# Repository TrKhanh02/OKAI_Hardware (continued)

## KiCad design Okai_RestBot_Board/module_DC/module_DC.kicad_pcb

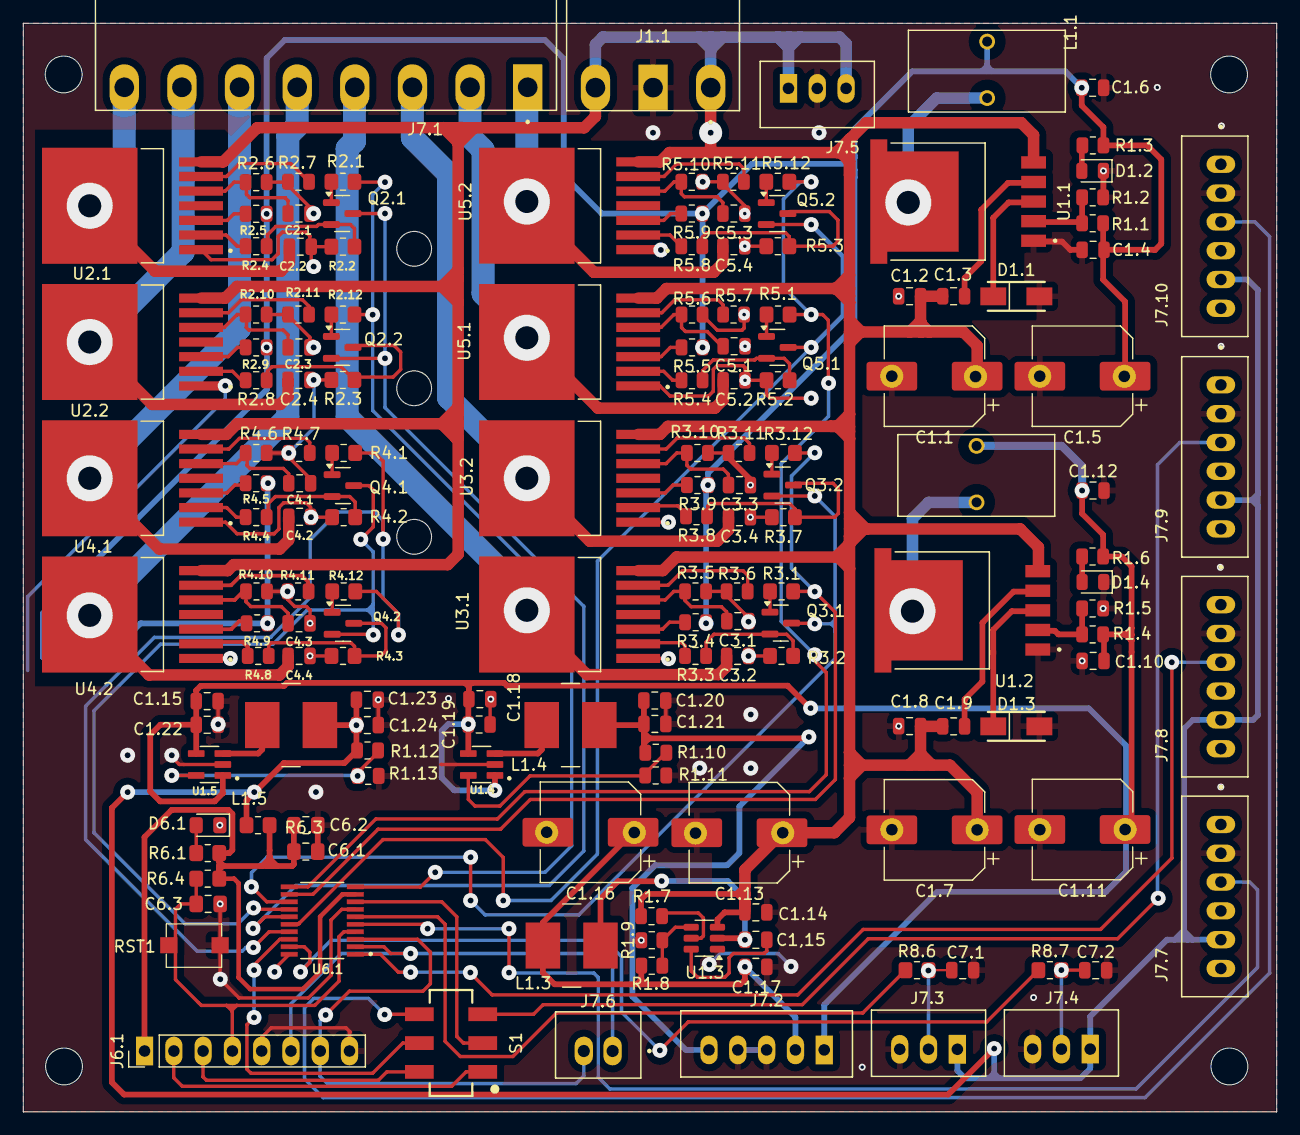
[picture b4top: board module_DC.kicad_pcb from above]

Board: 2 copper layers, 108.8 x 94.4 mm, 158 parts (0 on the bottom side), 102 nets.

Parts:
C1,15, C1.2, C1.6, C1.8, C1.12, C1.14, C1.19, C1.21, C1.22, C1.24, C2.1, C2.3, C3.1, C3.3, C4.1, C4.3, C5.1, C5.3, C7.1, C7.2: 104; C_0805_2012Metric
C1.1, C1.5, C1.7, C1.11, C1.13, C1.16: 220uF/25V; CP_Elec_8x10.5
C1.3, C1.4, C1.9, C1.10, C1.15, C1.17, C1.18, C1.20, C1.23, C2.2, C2.4, C3.2, C3.4, C4.2, C4.4, C5.2, C5.4: 106; C_0805_2012Metric
C6.1, C6.3: 104; C_0805_2012Metric_Pad1.18x1.45mm_HandSolder
C6.2: 10uF; C_0805_2012Metric_Pad1.18x1.45mm_HandSolder
D1.1, D1.3: SS54-HF; DIOM5025X220N
D1.2, D1.4: LED; LED_0805_2012Metric
D6.1: LED_Small_Filled; LED_0805_2012Metric_Pad1.15x1.40mm_HandSolder
J1.1: Nguon IN; CUI_TBP04R1-500-03BE
J6.1: Bootloader; PinHeader_1x08_P2.54mm_Vertical
J7.1: DC_12V; CUI_TBP04R1-500-08BE
J7.2: Nguon DK; JST_B5B-XH-A
J7.3: ROTATE1; JST_B3B-XH-A
J7.4: ROTATE2; JST_B3B-XH-A
J7.5: LOCK; JST_B3B-XH-A
J7.6: UART; JST_B2B-XH-A_LF__SN_
J7.7, J7.8: Rear drive motor; JST_B6B-XH-A_LF__SN_
J7.9: Rear axle motor; JST_B6B-XH-A_LF__SN_
J7.10: Front axle motor; JST_B6B-XH-A_LF__SN_
L1.1, L1.2: FIT68-3; IND_FIT68-3
L1.3, L1.4, L1.5: 22uH; L_Ferrocore_DLG-0705
Q2.1, Q3.1, Q4.1, Q5.1: SS8050; SOT-23
Q2.2, Q3.2, Q4.2, Q5.2: SS8550; SOT-23
R1.1, R1.4, R1.10, R1.12: 10K; R_0805_2012Metric
R1.2, R1.3, R1.5, R1.6: 3k3; R_0805_2012Metric
R1.7, R1.8: 10k; R_0805_2012Metric
R1.9, R2.4, R2.5, R2.6, R2.7, R2.8, R2.9, R2.10, R2.11, R3.3, R3.4, R3.5, R3.6, R3.8, R3.9, R3.10, R3.11, R4.4, R4.5, R4.6, R4.8, R4.9, R4.10, R5.4, R5.5, R5.6, R5.7, R5.8, R5.9, R5.10, R5.11: 1k8; R_0805_2012Metric
R1.11, R1.13: 2.2K; R_0805_2012Metric
R2.1, R2.2, R2.3, R2.12, R3.1, R3.2, R3.7, R3.12, R4.1, R4.2, R4.3, R4.12, R5.1, R5.2, R5.3, R5.12: 10K; R_0805_2012Metric_Pad1.20x1.40mm_HandSolder
R4.7: 1k; R_0805_2012Metric
R4.11: 1k6; R_0805_2012Metric
R6.1: 1K; R_0805_2012Metric_Pad1.20x1.40mm_HandSolder
R6.3: NC; R_0805_2012Metric_Pad1.20x1.40mm_HandSolder
R6.4: 10k; R_0805_2012Metric_Pad1.20x1.40mm_HandSolder
R8.6, R8.7: 0R; R_0805_2012Metric_Pad1.20x1.40mm_HandSolder
RST1: TS10-63-26-BE-250-SMT-TR; SW_TS10-63-26-BE-250-SMT-TR
S1: 452406020024
U1.1, U1.2: XL4015; CONV_XL4015
U1.3: TPS563201; SOT-23-6
U1.4, U1.5: TLV62569PDDCR; SOT95P280X110-6N
U2.1, U2.2, U3.1, U3.2, U4.1, U4.2, U5.1, U5.2: BTN7960B; DPAK127P1490X440-8N
U6.1: N76E003AT20; SOP65P640X120-20N

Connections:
/3.3V: C1.23.1, C1.24.1, J7.3.1, J7.4.1, J7.7.5, J7.8.5, J7.9.5, J7.10.5, L1.5.1, R1.12.2, R6.3.1
/3.3V_NV: C1.20.1, C1.21.1, J7.2.5, L1.4.1, R1.10.2
/5V_DC: C1.4.1, C1.5.1, C1.6.1, L1.1.2, R1.1.2, R1.3.2, R2.5.1, R2.9.1, R3.4.1, R3.9.1, R4.5.1, R4.9.1, R5.5.1, R5.9.1
/5V_MCU: C1.16.1, C1.17.1, J7.2.2, L1.3.1, R1.8.2
/5V_NV: C1.10.1, C1.11.1, C1.12.1, C1.15.1, C1.18.1, C1.19.1, C1.22.1, J7.2.1, L1.2.2, R1.4.2, R1.6.2, U1.4.1 (EN), U1.4.4 (VIN), U1.5.1 (EN), U1.5.4 (VIN)
/12V_DC: C1.1.1, C1.2.1, C1.3.1, C1.7.1, C1.8.1, C1.9.1, C1.13.1, C1.14.1, J1.1.1, J1.1.3, J7.5.1, J7.5.3, R1.7.2, U1.1.5 (VIN), U1.2.5 (VIN), U1.3.3 (VIN), U2.1.7 (VS), U2.2.7 (VS), U3.1.7 (VS), U3.2.7 (VS), U4.1.7 (VS), U4.2.7 (VS), U5.1.7 (VS), U5.2.7 (VS)
/+MT1: C2.2.2, J7.1.8, U2.1.4 (OUT), U2.1.8 (OUT)
/+MT2: C4.2.2, J7.1.6, U4.1.4 (OUT), U4.1.8 (OUT)
/+MT3: C3.2.2, J7.1.4, U3.1.4 (OUT), U3.1.8 (OUT)
/+MT4: C5.2.2, J7.1.2, U5.1.4 (OUT), U5.1.8 (OUT)
/-MT1: C2.4.2, J7.1.7, U2.2.4 (OUT), U2.2.8 (OUT)
/-MT2: C4.4.2, J7.1.5, U4.2.4 (OUT), U4.2.8 (OUT)
/-MT3: C3.4.2, J7.1.3, U3.2.4 (OUT), U3.2.8 (OUT)
/-MT4: C5.4.2, J7.1.1, U5.2.4 (OUT), U5.2.8 (OUT)
/A5.1: J7.7.3, U6.1.5 (P3.0/~INT0/OSCIN/AIN1)
/A5.2: J7.8.3, U6.1.1 (P0.5/PWM2/IC6/T0/AIN4)
/A5.3: J7.9.3, S1.2, S1.3, U6.1.8 (P1.6/[SDA]/TXD_1/ICPDA/OCDDA)
/A5.4: J7.10.3, S1.5, S1.6, U6.1.18 (P0.2/ICPCK/OCDCK/RXD_1/[SCL])
/Dir1: R2.1.1, R2.12.1, U6.1.10 (P1.5/PWM5/IC7/~SS)
/Dir2: R4.1.1, R4.12.1, U6.1.17 (P0.1/PWM4/IC4/MISO)
/Dir3: R3.1.1, R3.12.1, U6.1.12 (P1.3/SCL/[STADC])
/Dir4: R5.1.1, R5.12.1, U6.1.11 (P1.4/SDA/FB/PWM1)
/FB1: R1.10.1, R1.11.2, U1.4.6 (FB)
/FB2: R1.12.1, R1.13.2, U1.5.6 (FB)
/MST_RX2: J6.1.7, J7.6.2, U6.1.3 (P0.7/RXD/AIN2)
/MST_TX2: J6.1.6, J7.6.1, U6.1.2 (P0.6/TXD/AIN3)
/P0.0: Q5.1.3 (C), Q5.2.2 (E), U6.1.16 (P0.0/PWM3/IC3/MOSI/T1)
/P0.3: R8.7.1, U6.1.19 (P0.3/PWM5/IC5/AIN6)
/P1.0: Q2.1.3 (C), Q2.2.2 (E), U6.1.15 (P1.0/PWM2/IC2/SPCLK)
/P1.1: Q4.1.3 (C), Q4.2.2 (E), U6.1.14 (P1.1/PWM1/IC1/AIN7/CLO)
/P1.2: Q3.1.3 (C), Q3.2.2 (E), U6.1.13 (P1.2/PWM0/IC0)
/P1.7: R8.6.1, U6.1.6 (P1.7/~INT1/AIN0)
/P2.0: C6.3.1, J6.1.4, R6.4.2, RST1.2, U6.1.4 (P2.0/~RST)
/SIG1: C7.1.2, J7.3.2, R8.6.2
/SIG2: C7.2.2, J7.4.2, R8.7.2
/TICECLK: J6.1.3, S1.4
/TICEDAT: J6.1.2, S1.1
/VDD: C6.1.1, C6.2.1, J6.1.1, R6.1.1, R6.3.2, R6.4.1, U6.1.9 (VDD)
GND: C1.1.2, C1.2.2, C1.4.2, C1.5.2, C1.6.2, C1.7.2, C1.8.2, C1.10.2, C1.11.2, C1.12.2, C1.13.2, C1.14.2, C1.15.2, C1.16.2, C1.17.2, C1.18.2, C1.19.2, C1.20.2, C1.21.2, C1.22.2, C1.23.2, C1.24.2, C2.1.1, C2.2.1, C2.3.1, C2.4.1, C3.1.1, C3.2.1, C3.3.1, C3.4.1, C4.1.1, C4.2.1, C4.3.1, C4.4.1, C5.1.1, C5.2.1, C5.3.1, C5.4.1, C6.1.2, C6.2.2, C6.3.2, C7.1.1, C7.2.1, D1.1.2, D1.2.1 (K), D1.3.2, D1.4.1 (K), D6.1.1 (K), J1.1.2, J6.1.5, J6.1.8, J7.2.3, J7.2.4, J7.3.3, J7.4.3, J7.5.2, J7.7.2, J7.8.2, J7.9.2, J7.10.2, R1.2.1, R1.5.1, R1.9.2, R1.11.1, R1.13.1, R2.2.1, R2.3.1, R2.6.1, R2.7.2, R2.10.1, R2.11.2, R3.2.1, R3.5.1, R3.6.2, R3.7.1, R3.10.1, R3.11.2, R4.2.1, R4.3.1, R4.6.1, R4.7.2, R4.10.1, R4.11.2, R5.2.1, R5.3.1, R5.6.1, R5.7.2, R5.10.1, R5.11.2, RST1.1, U1.1.1 (GND), U1.2.1 (GND), U1.3.1 (GND), U1.4.2 (GND), U1.5.2 (GND), U2.1.1 (GND), U2.2.1 (GND), U3.1.1 (GND), U3.2.1 (GND), U4.1.1 (GND), U4.2.1 (GND), U5.1.1 (GND), U5.2.1 (GND), U6.1.7 (GND)
unnamed: D1.1.1, L1.1.1, U1.1.3 (SW), U1.1.3.1 (SW)
unnamed: D1.2.2 (A), R1.3.1
unnamed: D1.3.1, L1.2.1, U1.2.3 (SW), U1.2.3.1 (SW)
unnamed: D1.4.2 (A), R1.6.1
unnamed: D6.1.2 (A), R6.1.2
unnamed: Q2.1.1 (B), R2.1.2
unnamed: Q2.1.2 (E), R2.2.2, R2.4.1
unnamed: Q2.2.1 (B), R2.12.2
unnamed: Q2.2.3 (C), R2.3.2, R2.8.1
unnamed: Q3.1.1 (B), R3.1.2
unnamed: Q3.1.2 (E), R3.2.2, R3.3.1
unnamed: Q3.2.1 (B), R3.12.2
unnamed: Q3.2.3 (C), R3.7.2, R3.8.1
unnamed: Q4.1.1 (B), R4.1.2
unnamed: Q4.1.2 (E), R4.2.2, R4.4.1
unnamed: Q4.2.1 (B), R4.12.2
unnamed: Q4.2.3 (C), R4.3.2, R4.8.1
unnamed: Q5.1.1 (B), R5.1.2
unnamed: Q5.1.2 (E), R5.2.2, R5.4.1
unnamed: Q5.2.1 (B), R5.12.2
unnamed: Q5.2.3 (C), R5.3.2, R5.8.1
unnamed: R1.1.1, R1.2.2, U1.1.2 (FB)
unnamed: C1.3.2, U1.1.4 (VC)
unnamed: R1.4.1, R1.5.2, U1.2.2 (FB)
unnamed: C1.9.2, U1.2.4 (VC)
unnamed: R1.7.1, U1.3.5 (EN)
unnamed: C1,15.2, L1.3.2, U1.3.2 (SW)
unnamed: C1,15.1, U1.3.6 (VBST)
unnamed: R1.8.1, R1.9.1, U1.3.4 (VFB)
unnamed: L1.4.2, U1.4.3 (SW)
unnamed: L1.5.2, U1.5.3 (SW)
unnamed: R2.4.2, U2.1.2 (IN)
unnamed: R2.5.2, U2.1.3 (INH)
unnamed: R2.7.1, U2.1.6 (IS)
unnamed: C2.1.2, R2.6.2, U2.1.5 (SR)
unnamed: R2.8.2, U2.2.2 (IN)
unnamed: R2.9.2, U2.2.3 (INH)
unnamed: R2.11.1, U2.2.6 (IS)
unnamed: C2.3.2, R2.10.2, U2.2.5 (SR)
unnamed: R3.3.2, U3.1.2 (IN)
unnamed: R3.4.2, U3.1.3 (INH)
unnamed: R3.6.1, U3.1.6 (IS)
unnamed: C3.1.2, R3.5.2, U3.1.5 (SR)
unnamed: R3.8.2, U3.2.2 (IN)
unnamed: R3.9.2, U3.2.3 (INH)
unnamed: R3.11.1, U3.2.6 (IS)
unnamed: C3.3.2, R3.10.2, U3.2.5 (SR)
unnamed: R4.4.2, U4.1.2 (IN)
unnamed: R4.5.2, U4.1.3 (INH)
unnamed: R4.7.1, U4.1.6 (IS)
unnamed: C4.1.2, R4.6.2, U4.1.5 (SR)
unnamed: R4.8.2, U4.2.2 (IN)
unnamed: R4.9.2, U4.2.3 (INH)
unnamed: R4.11.1, U4.2.6 (IS)
unnamed: C4.3.2, R4.10.2, U4.2.5 (SR)
unnamed: R5.4.2, U5.1.2 (IN)
unnamed: R5.5.2, U5.1.3 (INH)
unnamed: R5.7.1, U5.1.6 (IS)
unnamed: C5.1.2, R5.6.2, U5.1.5 (SR)
unnamed: R5.8.2, U5.2.2 (IN)
unnamed: R5.9.2, U5.2.3 (INH)
unnamed: R5.11.1, U5.2.6 (IS)
unnamed: C5.3.2, R5.10.2, U5.2.5 (SR)

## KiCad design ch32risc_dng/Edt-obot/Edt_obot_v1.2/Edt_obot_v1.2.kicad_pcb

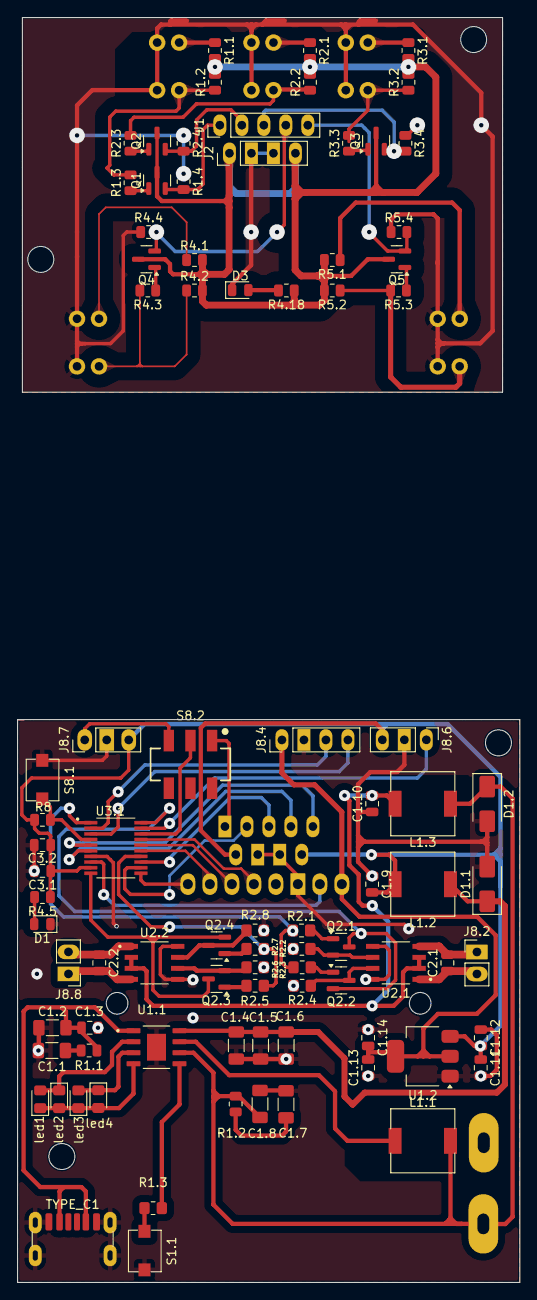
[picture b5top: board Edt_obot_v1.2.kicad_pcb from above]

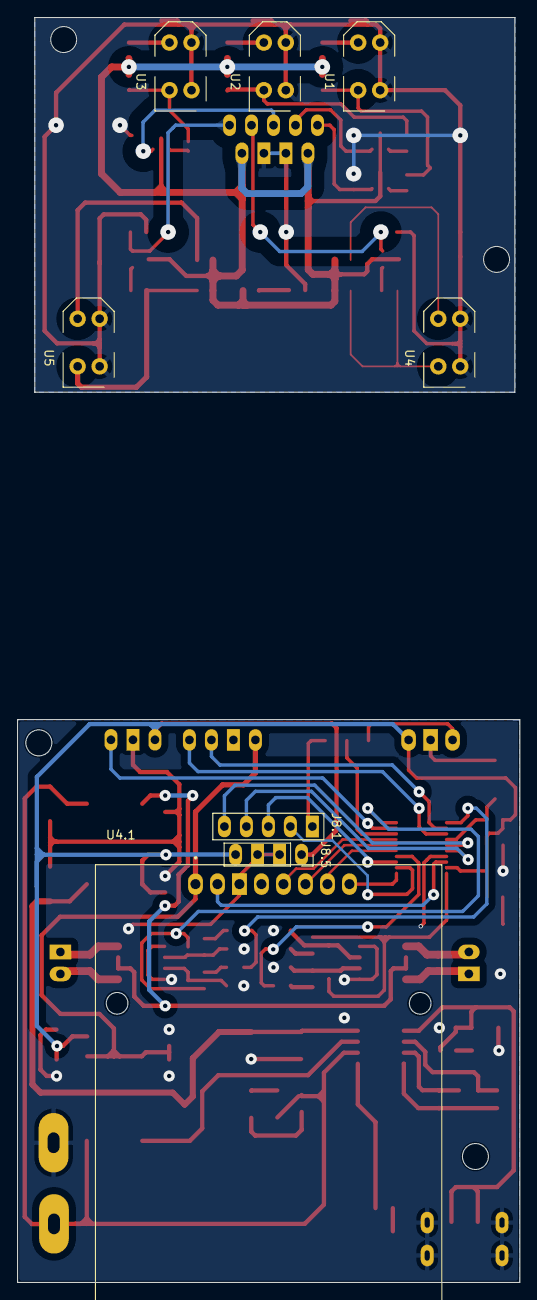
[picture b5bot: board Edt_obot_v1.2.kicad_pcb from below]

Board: 2 copper layers, 58.0 x 146.1 mm, 96 parts (8 on the bottom side), 71 nets.

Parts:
C1.1, C1.2: 106; C_1206_3216Metric_Pad1.33x1.80mm_HandSolder
C1.3, C1.12, C1.14, C2.1, C2.2, C3.1: 104; C_0805_2012Metric
C1.4, C1.5, C1.6: 22 UF; C_1206_3216Metric_Pad1.33x1.80mm_HandSolder
C1.7: 22uf; C_1206_3216Metric_Pad1.33x1.80mm_HandSolder
C1.8: 22uF; C_1206_3216Metric_Pad1.33x1.80mm_HandSolder
C1.9, C1.10, C1.11, C1.13, C3.2: 10uF; C_0805_2012Metric
D1: LEDPWR; LED_0805_2012Metric
D1.1, D1.2: SS34; D_SMA
D3: LED; LED_0805_2012Metric
J1: IR_LINE; PinHeader_1x05_P2.54mm_Vertical
J2: IR_LINE; PinHeader_1x04_P2.54mm_Vertical
J8.1: Conn_01x05_Pin; PinSocket_1x05_P2.54mm_Vertical
J8.2: MT1; PinHeader_1x02_P2.54mm_Vertical
J8.4: UART; PinHeader_1x04_P2.54mm_Vertical
J8.5: NGUON; PinSocket_1x04_P2.54mm_Vertical
J8.6: LED; PinHeader_1x03_P2.54mm_Vertical
J8.7: Upload; PinHeader_1x03_P2.54mm_Vertical
J8.8: MT2; PinHeader_1x02_P2.54mm_Vertical
L1.1: 1R; L_7.3x7.3_H4.5
L1.2, L1.3: L; L_7.3x7.3_H4.5
Q1, Q2, Q2.1, Q2.3, Q3, Q4, Q5: SS8050; SOT-23
Q2.2, Q2.4: SS8550; SOT-23
R1.1, R3.1, R4.1, R4.18, R5.1: 150R; R_0805_2012Metric
R1.1#2, R1.2#2: 2R; R_0805_2012Metric
R1.2, R1.4, R3.2, R3.4, R4.2, R4.4, R5.2, R5.4: 6.2k; R_0805_2012Metric
R1.3, R2.3#2, R3.3, R4.3, R4.5, R5.3: 1K; R_0805_2012Metric
R1.3#2: 10k; R_0805_2012Metric_Pad1.20x1.40mm_HandSolder
R2.1, R2.2, R2.3, R2.4, R2.5, R2.6, R2.7, R2.8: 10K; R_0805_2012Metric_Pad1.20x1.40mm_HandSolder
R2.1#2: 680R; R_0805_2012Metric
R2.2#2, R2.4#2, R8: 10K; R_0805_2012Metric
S1.1: TS10-63-26-BE-250-SMT-TR; SW_TS10-63-26-BE-250-SMT-TR
S8.1: RST; SW_TS10-63-26-BE-250-SMT-TR
S8.2: 452406020024
TYPE_C1: USB_C_Receptacle_PowerOnly_6P; USB_C_Receptacle_GCT_USB4125-xx-x_6P_TopMnt_Horizontal
U1, U2, U3, U4, U5: TCRT5000; OPTO_TCRT5000
U1.1: IP5306; SOP127P600X165-9N
U1.2: AMS1117-3.3; SOT-223-3_TabPin2
U2.1, U2.2: L9110S; SOIC127P599X172-8N
U3.1: CH32V003F4P6; SOP65P640X121-20N
U4.1: RFID; MODULE_CEG006900
led1: <25; LED_0805_2012Metric_Pad1.15x1.40mm_HandSolder
led2: <50; LED_0805_2012Metric_Pad1.15x1.40mm_HandSolder
led3: <75; LED_0805_2012Metric_Pad1.15x1.40mm_HandSolder
led4: >75; LED_0805_2012Metric_Pad1.15x1.40mm_HandSolder

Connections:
+5V: J2.1, J2.4, Q1.3 (C), Q2.3 (C), Q3.3 (C), Q4.3 (C), Q5.3 (C), R1.1.2, R1.2.2, R2.1#2.2, R2.2#2.2, R3.1.2, R3.2.2, R4.1.2, R4.2.2, R4.18.1, R5.1.2, R5.2.2
/2: U1.1.2 (LED1), led1.2 (A), led2.1 (K)
/3: U1.1.3 (LED2), led3.2 (A), led4.1 (K)
/3V3: C1.13.2, C1.14.2, J8.4.1, U1.2.2 (VO), U4.1.1 (VCC)
/3V7_BAT: C1.8.1, D1.2.1 (K), L1.1.2, L1.3.1, R1.2#2.2, U1.1.6 (BAT)
/4: U1.1.4 (LED3), led1.1 (K), led2.2 (A), led3.1 (K), led4.2 (A)
/5V: C1.9.2, C1.11.2, C1.12.2, C3.1.2, C3.2.2, J8.5.1, J8.5.4, J8.6.3, J8.7.3, L1.2.2, R4.5.1, R8.1, U1.2.3 (VI), U3.1.9 (VDD)
/5V_BAT: C1.4.2, C1.5.2, C1.6.2, D1.1.1 (K), L1.2.1, U1.1.8 (VOUT)
/5V_USB: C1.2.1, C1.3.1, R1.1#2.2, TYPE_C1.A9 (VBUS), TYPE_C1.B9 (VBUS), U1.1.1 (VIN)
/CS/SDA: U3.1.11 (PC1/SDA/NSS), U4.1.8 (SS/SDA/RX)
/Dir1: R2.1.1, R2.3.1, U3.1.1 (PD4/UCK/T2CH1ETR/A7/OPO)
/Dir2: R2.5.1, R2.7.1, U3.1.14 (PC4/T1CH4/MCO/A2)
/IA1: Q2.1.2 (E), R2.2.2, U2.1.6 (IA)
/IA2: Q2.3.2 (E), R2.6.2, U2.2.6 (IA)
/IB1: Q2.2.3 (C), R2.4.2, U2.1.7 (IB)
/IB2: Q2.4.3 (C), R2.8.2, U2.2.7 (IB)
/IR_LINE1: J1.1, Q1.2 (E), R1.4.2
/IR_LINE2: J1.2, Q2.2 (E), R2.4#2.2
/IR_LINE3: J1.3, Q3.2 (E), R3.4.2
/IR_LINE4: J1.4, Q4.2 (E), R4.4.2
/IR_LINE5: J1.5, Q5.2 (E), R5.4.2
/LINE1: J8.1.1, S8.2.1
/LINE2: J8.1.2, U3.1.12 (PC2/SCL/URTS/T1BKIN)
/LINE3: J8.1.3, U3.1.13 (PC3/T1CH3)
/LINE4: J8.1.4, U3.1.6 (PA2/TICH2N/A0/OPP0)
/LINE5: J8.1.5, U3.1.5 (PA1/T1CH2/A1/OPN0)
/MISO: U3.1.17 (PC7/MISO), U4.1.5 (MISO/SCL/TX)
/MOSI: U3.1.16 (PC6/MOSI), U4.1.6 (MOSI)
/OA1: C2.1.1, J8.2.2, U2.1.1 (OA)
/OA2: C2.2.1, J8.8.2, U2.2.1 (OA)
/OB1: C2.1.2, J8.2.1, U2.1.4 (OB)
/OB2: C2.2.2, J8.8.1, U2.2.4 (OB)
/PD1: S8.2.2, U3.1.18 (PD1/SWIO/T1CH3N/AETR2)
/PWM1: Q2.1.3 (C), Q2.2.2 (E), U3.1.20 (PD3/A4/T2CH2/AETR/UCTS)
/PWM2: Q2.3.3 (C), Q2.4.2 (E), U3.1.10 (PC0/T2CH3)
/RST: R8.2, S8.1.2, U3.1.4 (PD7/~RST/T2CH4/OPP1)
/RST_RFID: U3.1.8 (PD0/TICH1N/OPN1), U4.1.2 (RST)
/SCK: U3.1.15 (PC5/SCK/T1ETR), U4.1.7 (SCK)
/SENSE: C1.7.1, R1.2#2.1
/SWD: J8.7.1, S8.2.3
/URX: J8.4.4, U3.1.3 (PD6/URX/A6)
/UTX: J8.4.3, U3.1.2 (PD5/UTX/A5)
/WS2812: J8.6.1, U3.1.19 (PD2/T1CH1/A3)
GND: C1.1.2, C1.2.2, C1.3.2, C1.4.1, C1.5.1, C1.6.1, C1.7.2, C1.8.2, C1.9.1, C1.10.1, C1.11.1, C1.12.1, C1.13.1, C1.14.1, C3.1.1, C3.2.1, D1.1 (K), D1.1.2 (A), D1.2.2 (A), J8.4.2, J8.5.2, J8.5.3, J8.6.2, J8.7.2, R2.2.1, R2.4.1, R2.6.1, R2.8.1, S1.1.2, S8.1.1, TYPE_C1.A12 (GND), TYPE_C1.B12 (GND), TYPE_C1.S1 (SHIELD), U1.1.9 (POWERPAD), U1.2.1 (GND), U2.1.5 (GND), U2.1.8 (GND), U2.2.5 (GND), U2.2.8 (GND), U3.1.7 (VSS), U4.1.3 (GND)
GND0: D3.1 (K), J2.2, J2.3, R1.4.1, R2.4#2.1, R3.4.1, R4.4.1, R5.4.1, U1.CATH, U1.E, U2.CATH, U2.E, U3.CATH, U3.E, U4.CATH, U4.E, U5.CATH, U5.E
unnamed: C1.1.1, R1.1#2.1
unnamed: D1.2 (A), R4.5.2
unnamed: D3.2 (A), R4.18.2
unnamed: Q1.1 (B), R1.3.1
unnamed: Q2.1 (B), R2.3#2.1
unnamed: Q2.1.1 (B), R2.1.2
unnamed: Q2.2.1 (B), R2.3.2
unnamed: Q2.3.1 (B), R2.5.2
unnamed: Q2.4.1 (B), R2.7.2
unnamed: Q3.1 (B), R3.3.1
unnamed: Q4.1 (B), R4.3.1
unnamed: Q5.1 (B), R5.3.1
unnamed: R1.1.1, U1.A
unnamed: R1.2.1, R1.3.2, U1.COLL
unnamed: R1.3#2.2, S1.1.1
unnamed: R2.1#2.1, U2.A
unnamed: R2.2#2.1, R2.3#2.2, U2.COLL
unnamed: R3.1.1, U3.A
unnamed: R3.2.1, R3.3.2, U3.COLL
unnamed: R4.1.1, U4.A
unnamed: R4.2.1, R4.3.2, U4.COLL
unnamed: R5.1.1, U5.A
unnamed: R5.2.1, R5.3.2, U5.COLL
unnamed: R1.3#2.1, U1.1.5 (KEY)
unnamed: L1.1.1, U1.1.7 (SW)
VCC: C1.10.2, L1.3.2, U2.1.2 (VCC), U2.1.3 (VCC), U2.2.2 (VCC), U2.2.3 (VCC)
